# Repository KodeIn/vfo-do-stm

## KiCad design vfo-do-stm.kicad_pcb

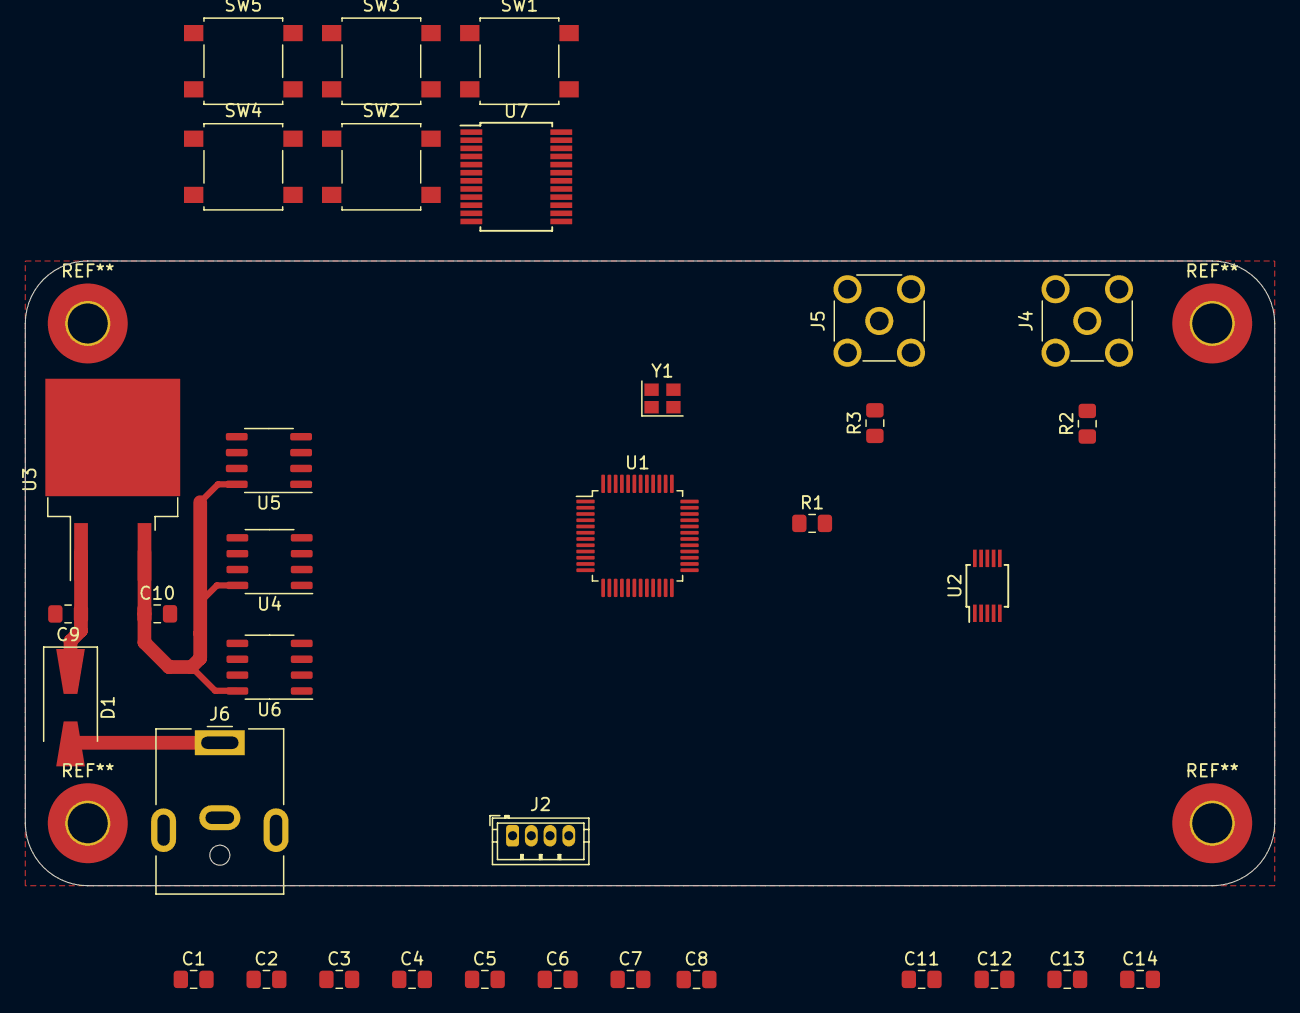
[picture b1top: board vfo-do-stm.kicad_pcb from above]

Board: 2 copper layers, 100.0 x 50.0 mm, 35 parts (0 on the bottom side), 25 nets.

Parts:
C1, C2: 20pF; C_0805_2012Metric_Pad1.15x1.40mm_HandSolder
C3: 1µF; C_0805_2012Metric_Pad1.15x1.40mm_HandSolder
C4: 100nF; C_0805_2012Metric_Pad1.15x1.40mm_HandSolder
C5, C6: 0.47µF; C_0805_2012Metric_Pad1.15x1.40mm_HandSolder
C7, C10, C11, C13: 0.1µF; C_0805_2012Metric_Pad1.15x1.40mm_HandSolder
C8, C12, C14: 10µF; C_0805_2012Metric_Pad1.15x1.40mm_HandSolder
C9: 0.33µF; C_0805_2012Metric_Pad1.15x1.40mm_HandSolder
D1: D_Schottky; D_SMA-SMB_Universal_Handsoldering
J2: SWIM; JST_ZH_B4B-ZR_1x04_P1.50mm_Vertical
J4: LO; SMA_Molex_73251-2200_Horizontal
J5: VFO; SMA_Molex_73251-2200_Horizontal
J6: DC_in; BarrelJack_CUI_PJ-063AH_Horizontal
R1, R2, R3: 0Ω; R_0805_2012Metric_Pad1.15x1.40mm_HandSolder
SW1: BP1; SW_SPST_B3S-1000
SW2: BP2; SW_SPST_B3S-1000
SW3: BP3; SW_SPST_B3S-1000
SW4: BP4; SW_SPST_B3S-1000
SW5: SW_NRST; SW_SPST_B3S-1000
U1: STM8S208C8; LQFP-48_7x7mm_P0.5mm
U2: Si5351A-B-GT; MSOP-10_3x3mm_P0.5mm
U3: L7805; TO-263-2
U4, U5, U6: LE33CD; SO-8_3.9x4.9mm_P1.27mm
U7: TCA9535DBR; SSOP-24_5.3x8.2mm_P0.65mm
Y1: 24MHz; Crystal_SMD_2520-4Pin_2.5x2.0mm

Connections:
3.3CLK: C5.1, C6.1, C14.1, U2.1, U2.7, U6.1
/Alimentation/3.3_LCD: C12.1, U5.1
/Alimentation/3.3_MCU: C8.1, J2.1, U1.7, U1.8, U1.13, U1.32, U4.1
/Alimentation/Net_5.5V: C7.1, C10.1, C11.1, C13.1, U3.3, U4.8, U5.8, U6.8
GND: C1.2, C2.2, C3.2, C4.2, C5.2, C6.2, C7.2, C8.2, C9.2, C10.2, C11.2, C12.2, C13.2, C14.2, J2.3, J4.2, J5.2, J6.2, SW1.2, SW2.2, SW3.2, SW4.2, U1.4, U1.5, U1.14, U1.31, U2.8, U3.2, U4.2, U4.3, U4.5, U4.6, U4.7, U5.2, U5.3, U5.6, U5.7, U6.2, U6.3, U6.6, U6.7, Y1.2, Y1.4
INH_CLK: U1.39, U6.5
INH_LCD: U1.40, U5.5
I²C_SCL: U1.18, U2.4
I²C_SDA: U1.17, U2.5
NRST: C4.1, J2.4, U1.1
unnamed: C1.1, U1.2, Y1.3
unnamed: C2.1, U1.3, Y1.1
unnamed: C3.1, U1.6
unnamed: C9.1, D1.1, U3.1
unnamed: D1.2, J6.1
unnamed: J2.2, U1.42
unnamed: J4.1, R2.2
unnamed: J5.1, R3.2
unnamed: R1.2, U2.10
unnamed: R2.1, U2.6
unnamed: R3.1, U2.9
unnamed: SW1.1, U7.4
unnamed: SW2.1, U7.5
unnamed: SW3.1, U7.6
unnamed: SW4.1, U7.7

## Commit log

2020-08-19 Ebauche pcb + ajouts schema
2020-08-20 Améliorations ébauche PCB
    Ajout contour
    Changement d'empreinte pour D1, J3, J4
    Certains filtrages, découplages, résistance pullup/polldown sont encore manquants.
2020-08-20 Update vfo-do-stm.kicad_pcb
    Essai de placement MCU et réguls 3.3V
2020-08-20 Ebauche ecran
    Ajout connecteur pour afficheur oled https://www.buydisplay.com/yellow-2-4-inch-graphic-oled-display-128x64-serial-spi-i2c-ssd1309
    Renommage nets GPS -> CLK
2020-08-23 Changement régul 3.3V & ajout expander I²C
    Refonte de l'étage d'alim
    Ajout d'une extension de 16 I/O en I²C
    Retrait du connecteur écran
    Ajout d'un crystal 24MHz pour le MCU
2020-08-24 Répartition des éléments du schéma en feuilles hiérarchiques
    petites modifs du pcb
